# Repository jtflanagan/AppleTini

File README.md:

# AppleTini
An FPGA-based multifunctional card

Earlier iterations of the design used microcontrollers (a Pico and a Teensy 4.1), but we have moved to an FPGA-based design.  The v4 version of the board works in an Apple IIe as a read-only bus dump card.  It reads events on the Apple II bus, and forwards them over USB to a remote host which can process them (including operating as HDMI video-out, similar to the VidHD card).

The v5 board (just ordered!) is intended to provide the full bus feature set.  The ability to read and write data to the bus, as well as perform full DMA and assert all the control lines available (DMA, RES, RDY, INH, IRQ, NMI, and properly implement DMAIN/OUT and INTIN/OUT.

The boards are designed to connect to a stack of Alchitry boards as sold by SparkFun.  The boards have headers which will mate with the Alchitry Br breakout board.  The high-speed USB needed to do bus dumping is provided by the Alchitry Ft board, which is capable of up to 1.6Gbits/sec data transmit over USB3.  The FPGA, and 256MB of DDR3 SDRAM is provided by the Alchitry Au board.

What can this board ultimately do?  Damn near anything.  Shorter term goals are to provide HDMI out, speaker sound, Mockingboard sound, mouse, Ramworks or Slinky style memory expansion, and solid state HDV storage.  Longer term?  CPU Acceleration.  In-circuit Emulator level debugging.  More flexible expanded memory banking techniques.  There's a lot of potential!  The FPGA on the Alchitry Au is an Artix-7 35T, so there's a lot of room for all kinds of stuff.

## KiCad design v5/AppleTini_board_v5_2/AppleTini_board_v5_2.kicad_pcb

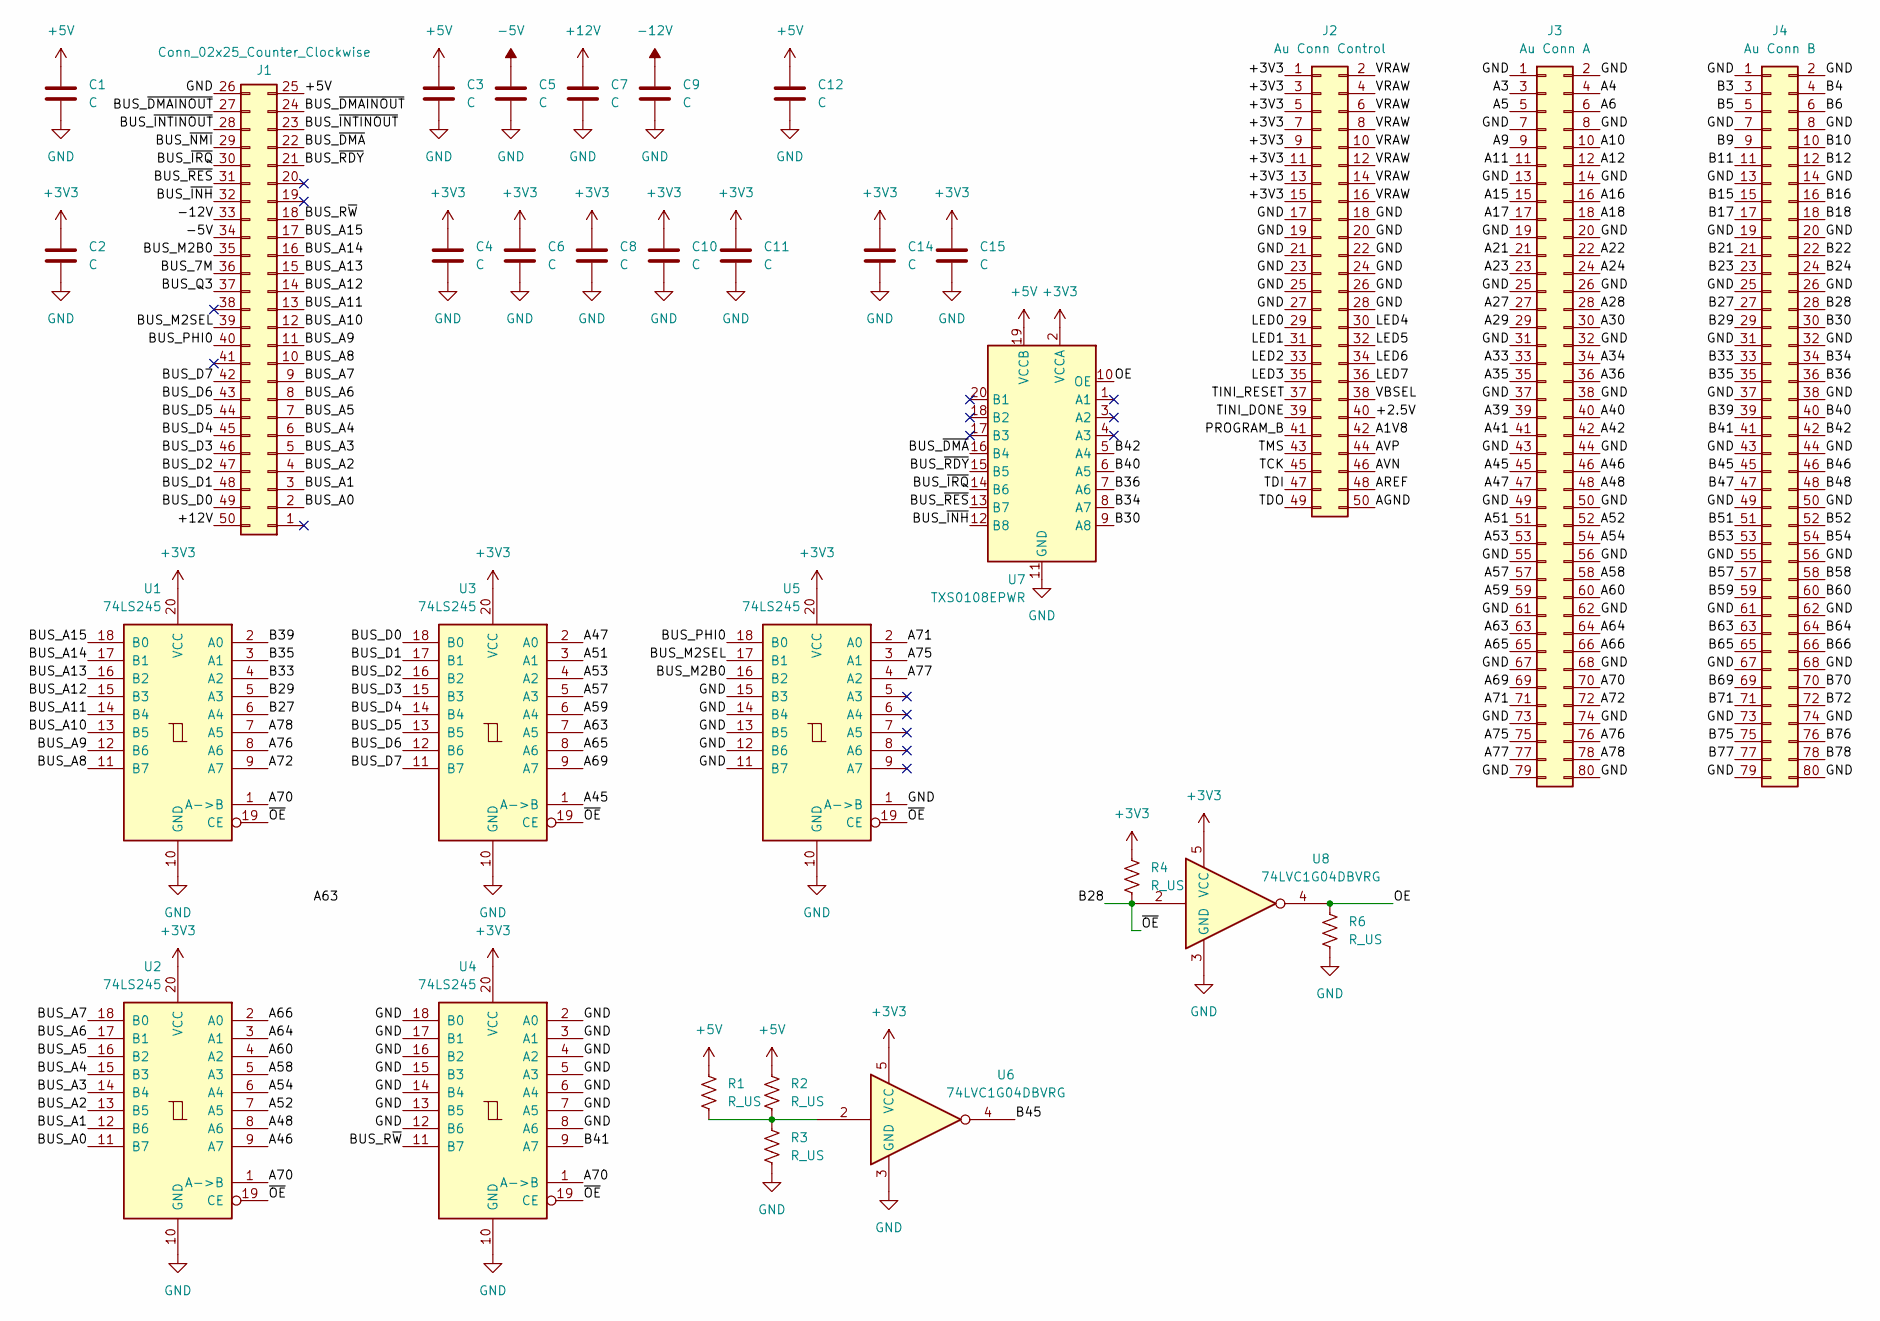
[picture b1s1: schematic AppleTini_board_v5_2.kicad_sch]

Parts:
C1, C2: C; C_0805_2012Metric; LCSC C440198
C3, C4, C5, C6, C7, C8, C9, C10, C11, C12, C14, C15: C; C_0402_1005Metric; LCSC C77020
J1: Conn_02x25_Counter_Clockwise; AppleIIBus_Edge
J2: Au Conn Control; CONN50_6p6X2p9_hdr_HIR; LCSC C424645
J3: Au Conn A; CONN80_17p5X1p85_hdr_HIR; LCSC C294544
J4: Au Conn B; CONN80_17p5X1p85_hdr_HIR; LCSC C294544
R1, R2, R3, R4, R6: R_US; R_0402_1005Metric; LCSC C2991755
U1, U2, U3, U4, U5: 74LS245; TSSOP-20_4.4x6.5mm_P0.65mm; LCSC C6082
U6, U8: 74LVC1G04DBVRG; SOT-353_SC-70-5; LCSC C264081
U7: TXS0108EPWR; TSSOP-20_4.4x6.5mm_P0.65mm; LCSC C17206

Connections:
+3V3: C2.1, C4.1, C6.1, C8.1, C10.1, C11.1, C14.1, C15.1, J2.1, J2.3, J2.5, J2.7, J2.9, J2.11, J2.13, J2.15, R4.1, U1.20 (VCC), U2.20 (VCC), U3.20 (VCC), U4.20 (VCC), U5.20 (VCC), U6.5 (VCC), U7.2 (VCCA), U8.5 (VCC)
+5V: C1.1, C3.1, C12.1, J1.25, R1.1, R2.1, U7.19 (VCCB)
+12V: C7.1, J1.50
-5V: C5.1, J1.34
-12V: C9.1, J1.33
/+2.5V: J2.40
/A1V8: J2.42
/A3: J3.3
/A4: J3.4
/A5: J3.5
/A6: J3.6
/A9: J3.9
/A10: J3.10
/A11: J3.11
/A12: J3.12
/A15: J3.15
/A16: J3.16
/A17: J3.17
/A18: J3.18
/A21: J3.21
/A22: J3.22
/A23: J3.23
/A24: J3.24
/A27: J3.27
/A28: J3.28
/A29: J3.29
/A30: J3.30
/A33: J3.33
/A34: J3.34
/A35: J3.35
/A36: J3.36
/A39: J3.39
/A40: J3.40
/A41: J3.41
/A42: J3.42
/A45: J3.45, U3.1 (A->B)
/A46: J3.46, U2.9 (A7)
/A47: J3.47, U3.2 (A0)
/A48: J3.48, U2.8 (A6)
/A51: J3.51, U3.3 (A1)
/A52: J3.52, U2.7 (A5)
/A53: J3.53, U3.4 (A2)
/A54: J3.54, U2.6 (A4)
/A57: J3.57, U3.5 (A3)
/A58: J3.58, U2.5 (A3)
/A59: J3.59, U3.6 (A4)
/A60: J3.60, U2.4 (A2)
/A63: J3.63, U3.7 (A5)
/A64: J3.64, U2.3 (A1)
/A65: J3.65, U3.8 (A6)
/A66: J3.66, U2.2 (A0)
/A69: J3.69, U3.9 (A7)
/A70: J3.70, U1.1 (A->B), U2.1 (A->B), U4.1 (A->B)
/A71: J3.71, U5.2 (A0)
/A72: J3.72, U1.9 (A7)
/A75: J3.75, U5.3 (A1)
/A76: J3.76, U1.8 (A6)
/A77: J3.77, U5.4 (A2)
/A78: J3.78, U1.7 (A5)
/AGND: J2.50
/AREF: J2.48
/AVN: J2.46
/AVP: J2.44
/B3: J4.3
/B4: J4.4
/B5: J4.5
/B6: J4.6
/B9: J4.9
/B10: J4.10
/B11: J4.11
/B12: J4.12
/B15: J4.15
/B16: J4.16
/B17: J4.17
/B18: J4.18
/B21: J4.21
/B22: J4.22
/B23: J4.23
/B24: J4.24
/B27: J4.27, U1.6 (A4)
/B28: J4.28, R4.2, U1.19 (CE), U2.19 (CE), U3.19 (CE), U4.19 (CE), U5.19 (CE), U8.2
/B29: J4.29, U1.5 (A3)
/B30: J4.30, U7.9 (A8)
/B33: J4.33, U1.4 (A2)
/B34: J4.34, U7.8 (A7)
/B35: J4.35, U1.3 (A1)
/B36: J4.36, U7.7 (A6)
/B39: J4.39, U1.2 (A0)
/B40: J4.40, U7.6 (A5)
/B41: J4.41, U4.9 (A7)
/B42: J4.42, U7.5 (A4)
/B45: J4.45, U6.4
/B46: J4.46
/B47: J4.47
/B48: J4.48
/B51: J4.51
/B52: J4.52
/B53: J4.53
/B54: J4.54
/B57: J4.57
/B58: J4.58
/B59: J4.59
/B60: J4.60
/B63: J4.63
/B64: J4.64
/B65: J4.65
/B66: J4.66
/B69: J4.69
/B70: J4.70
/B71: J4.71
/B72: J4.72
/B75: J4.75
/B76: J4.76
/B77: J4.77
/B78: J4.78
/BUS_7M: J1.36
/BUS_A0: J1.2, U2.11 (B7)
/BUS_A1: J1.3, U2.12 (B6)
/BUS_A2: J1.4, U2.13 (B5)
/BUS_A3: J1.5, U2.14 (B4)
/BUS_A4: J1.6, U2.15 (B3)
/BUS_A5: J1.7, U2.16 (B2)
/BUS_A6: J1.8, U2.17 (B1)
/BUS_A7: J1.9, U2.18 (B0)
/BUS_A8: J1.10, U1.11 (B7)
/BUS_A9: J1.11, U1.12 (B6)
/BUS_A10: J1.12, U1.13 (B5)
/BUS_A11: J1.13, U1.14 (B4)
/BUS_A12: J1.14, U1.15 (B3)
/BUS_A13: J1.15, U1.16 (B2)
/BUS_A14: J1.16, U1.17 (B1)
/BUS_A15: J1.17, U1.18 (B0)
/BUS_D0: J1.49, U3.18 (B0)
/BUS_D1: J1.48, U3.17 (B1)
/BUS_D2: J1.47, U3.16 (B2)
/BUS_D3: J1.46, U3.15 (B3)
/BUS_D4: J1.45, U3.14 (B4)
/BUS_D5: J1.44, U3.13 (B5)
/BUS_D6: J1.43, U3.12 (B6)
/BUS_D7: J1.42, U3.11 (B7)
/BUS_M2B0: J1.35, U5.16 (B2)
/BUS_M2SEL: J1.39, U5.17 (B1)
/BUS_PHI0: J1.40, U5.18 (B0)
/BUS_Q3: J1.37
/BUS_R~W: J1.18, U4.11 (B7)
/BUS_~DMAINOUT: J1.24, J1.27
/BUS_~DMA: J1.22, U7.16 (B4)
/BUS_~INH: J1.32, U7.12 (B8)
/BUS_~INTINOUT: J1.23, J1.28
/BUS_~IRQ: J1.30, U7.14 (B6)
/BUS_~NMI: J1.29
/BUS_~RDY: J1.21, U7.15 (B5)
/BUS_~RES: J1.31, U7.13 (B7)
/LED0: J2.29
/LED1: J2.31
/LED2: J2.33
/LED3: J2.35
/LED4: J2.30
/LED5: J2.32
/LED6: J2.34
/LED7: J2.36
/OE: R6.1, U7.10 (OE), U8.4
/PROGRAM_B: J2.41
/TCK: J2.45
/TDI: J2.47
/TDO: J2.49
/TINI_DONE: J2.39
/TINI_RESET: J2.37
/TMS: J2.43
/VBSEL: J2.38
/VRAW: J2.2, J2.4, J2.6, J2.8, J2.10, J2.12, J2.14, J2.16
GND: C1.2, C2.2, C3.2, C4.2, C5.2, C6.2, C7.2, C8.2, C9.2, C10.2, C11.2, C12.2, C14.2, C15.2, J1.26, J2.17, J2.18, J2.19, J2.20, J2.21, J2.22, J2.23, J2.24, J2.25, J2.26, J2.27, J2.28, J3.1, J3.2, J3.7, J3.8, J3.13, J3.14, J3.19, J3.20, J3.25, J3.26, J3.31, J3.32, J3.37, J3.38, J3.43, J3.44, J3.49, J3.50, J3.55, J3.56, J3.61, J3.62, J3.67, J3.68, J3.73, J3.74, J3.79, J3.80, J4.1, J4.2, J4.7, J4.8, J4.13, J4.14, J4.19, J4.20, J4.25, J4.26, J4.31, J4.32, J4.37, J4.38, J4.43, J4.44, J4.49, J4.50, J4.55, J4.56, J4.61, J4.62, J4.67, J4.68, J4.73, J4.74, J4.79, J4.80, R3.2, R6.2, U1.10 (GND), U2.10 (GND), U3.10 (GND), U4.2 (A0), U4.3 (A1), U4.4 (A2), U4.5 (A3), U4.6 (A4), U4.7 (A5), U4.8 (A6), U4.10 (GND), U4.12 (B6), U4.13 (B5), U4.14 (B4), U4.15 (B3), U4.16 (B2), U4.17 (B1), U4.18 (B0), U5.1 (A->B), U5.10 (GND), U5.11 (B7), U5.12 (B6), U5.13 (B5), U5.14 (B4), U5.15 (B3), U6.3 (GND), U7.11 (GND), U8.3 (GND)
unnamed: R1.2, R2.2, R3.1, U6.2

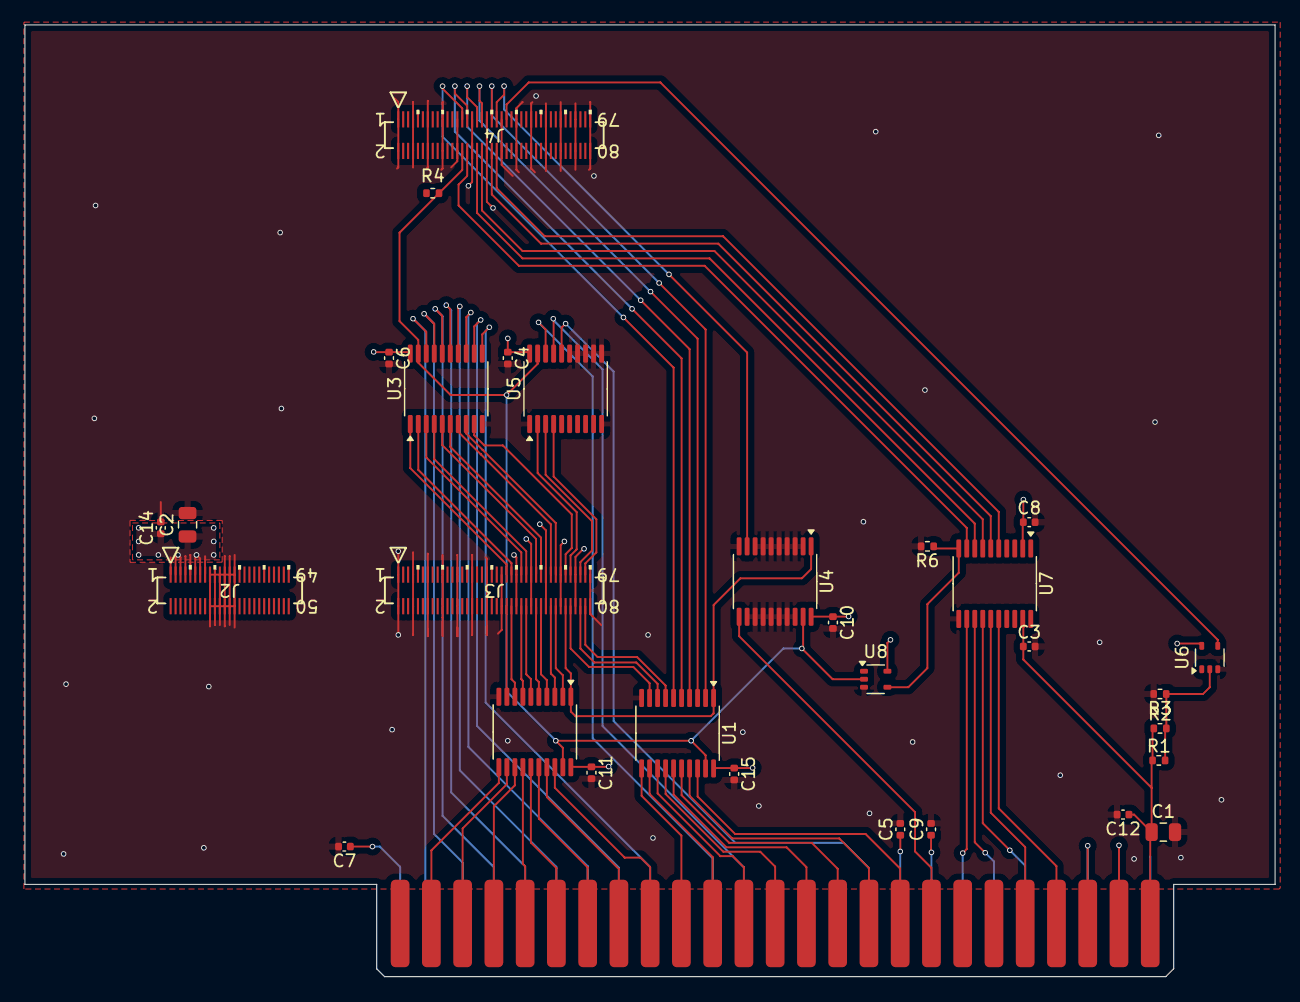
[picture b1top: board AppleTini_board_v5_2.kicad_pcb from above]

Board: 4 copper layers, 101.6 x 77.3 mm, 31 parts (0 on the bottom side), 81 nets.

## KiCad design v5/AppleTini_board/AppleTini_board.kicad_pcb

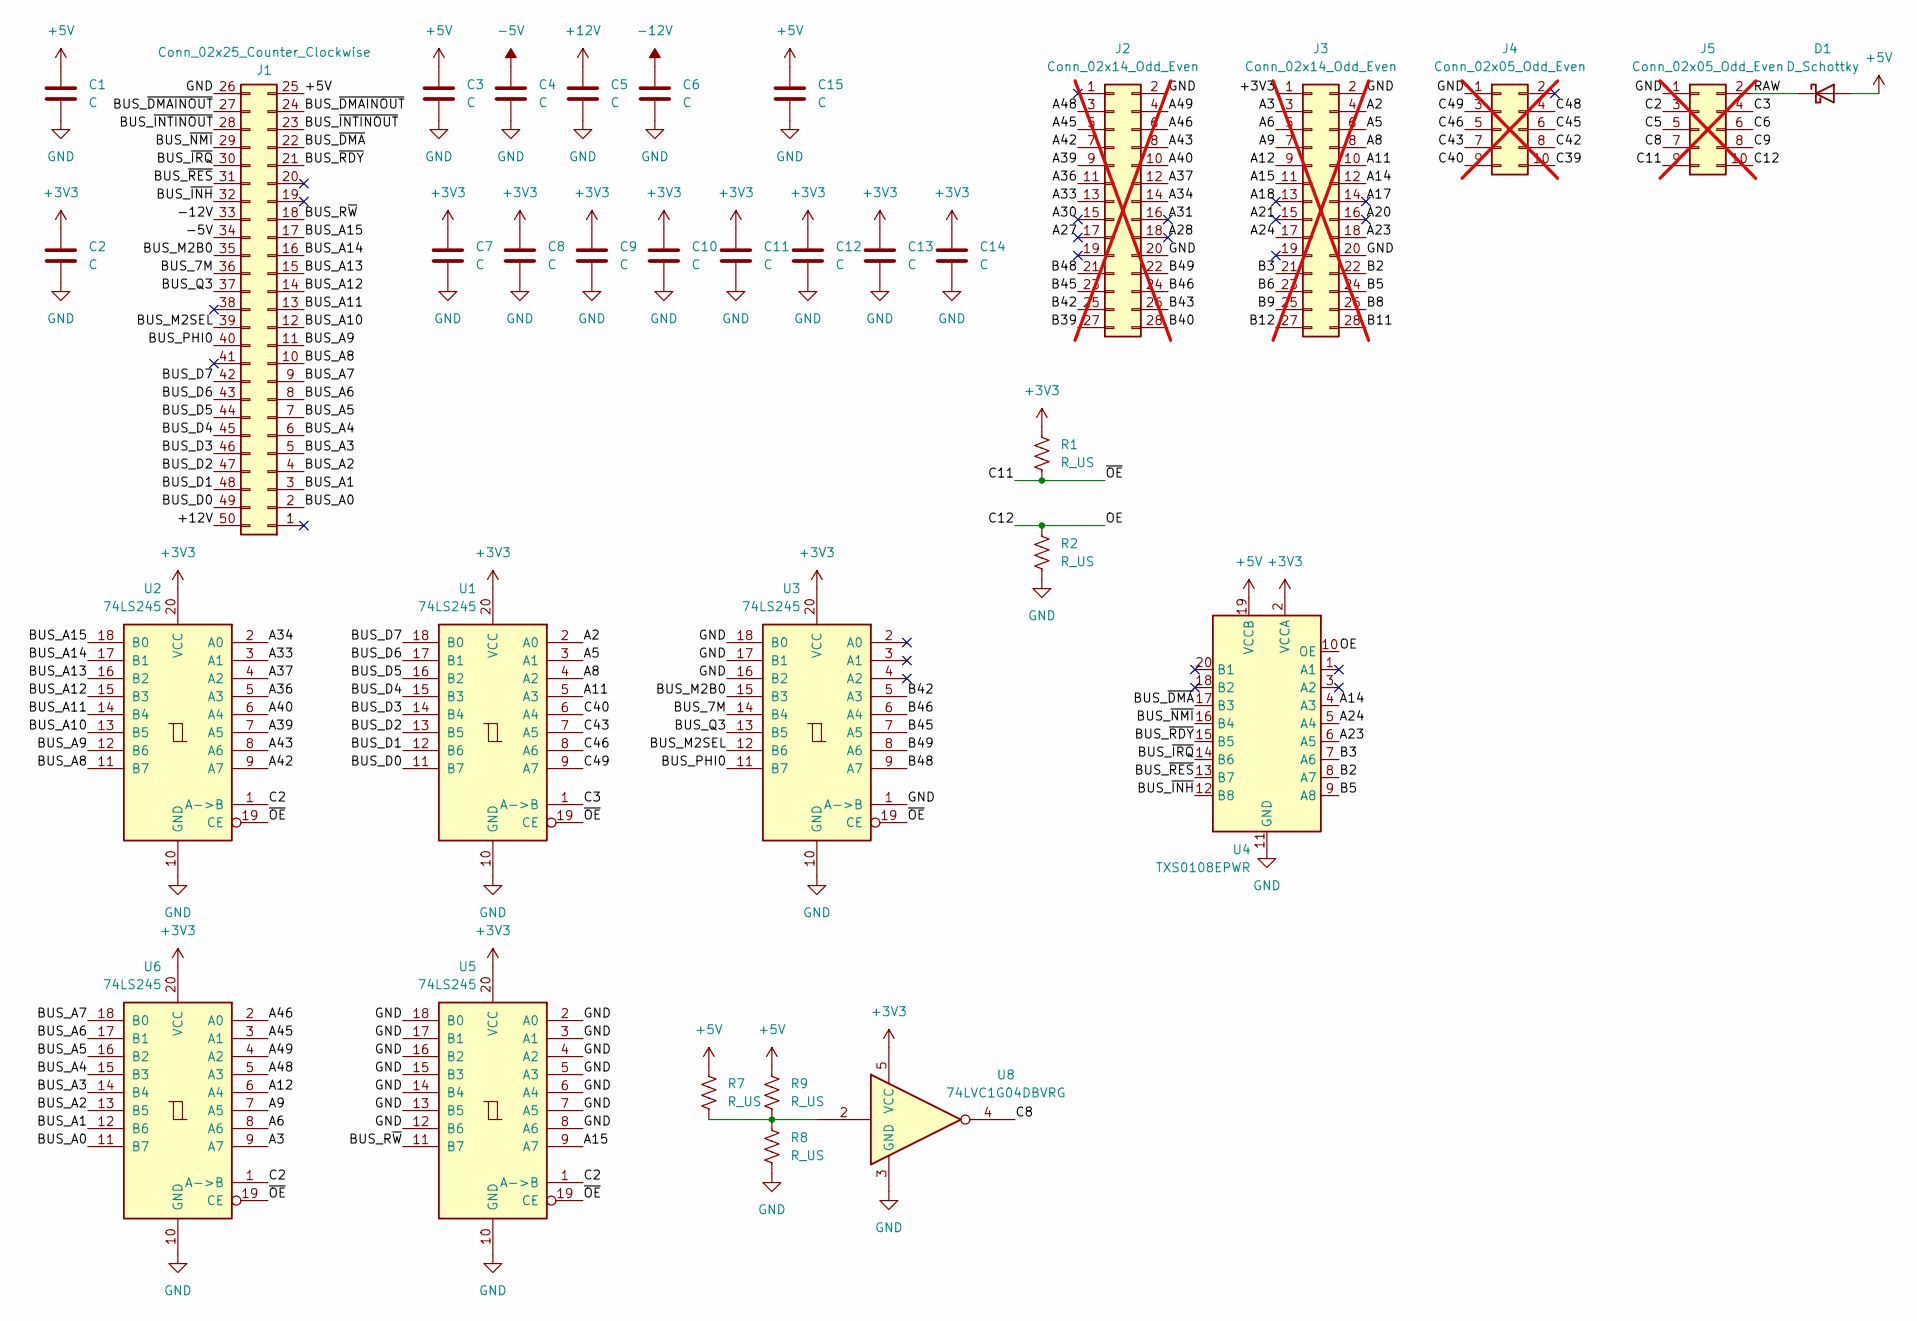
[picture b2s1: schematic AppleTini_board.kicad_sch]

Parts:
C1, C2: C; C_0805_2012Metric; LCSC C440198
C3, C4, C5, C6, C7, C8, C9, C10, C11, C12, C13, C14, C15: C; C_0402_1005Metric; LCSC C77020
D1: D_Schottky; Nexperia_CFP3_SOD-123W; LCSC C82288
J1: Conn_02x25_Counter_Clockwise; AppleIIBus_Edge
J2, J3: Conn_02x14_Odd_Even; PinHeader_2x14_P2.54mm_Vertical; not fitted
J4, J5: Conn_02x05_Odd_Even; PinHeader_2x05_P2.54mm_Vertical; not fitted
R1, R2, R7, R8, R9: R_US; R_0402_1005Metric; LCSC C2991755
U1, U2, U3, U5, U6: 74LS245; TSSOP-20_4.4x6.5mm_P0.65mm; LCSC C6082
U4: TXS0108EPWR; TSSOP-20_4.4x6.5mm_P0.65mm; LCSC C17206
U8: 74LVC1G04DBVRG; SOT-23-5

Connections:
+3V3: C2.1, C7.1, C8.1, C9.1, C10.1, C11.1, C12.1, C13.1, C14.1, J3.1, R1.1, U1.20 (VCC), U2.20 (VCC), U3.20 (VCC), U4.2 (VCCA), U5.20 (VCC), U6.20 (VCC), U8.5 (VCC)
+5V: C1.1, C3.1, C15.1, D1.2 (A), J1.25, R7.1, R9.1, U4.19 (VCCB)
+12V: C5.1, J1.50
-5V: C4.1, J1.34
-12V: C6.1, J1.33
/A2: J3.4, U1.2 (A0)
/A3: J3.3, U6.9 (A7)
/A5: J3.6, U1.3 (A1)
/A6: J3.5, U6.8 (A6)
/A8: J3.8, U1.4 (A2)
/A9: J3.7, U6.7 (A5)
/A11: J3.10, U1.5 (A3)
/A12: J3.9, U6.6 (A4)
/A14: J3.12, U4.4 (A3)
/A15: J3.11, U5.9 (A7)
/A17: J3.14
/A18: J3.13
/A20: J3.16
/A21: J3.15
/A23: J3.18, U4.6 (A5)
/A24: J3.17, U4.5 (A4)
/A27: J2.17
/A28: J2.18
/A30: J2.15
/A31: J2.16
/A33: J2.13, U2.3 (A1)
/A34: J2.14, U2.2 (A0)
/A36: J2.11, U2.5 (A3)
/A37: J2.12, U2.4 (A2)
/A39: J2.9, U2.7 (A5)
/A40: J2.10, U2.6 (A4)
/A42: J2.7, U2.9 (A7)
/A43: J2.8, U2.8 (A6)
/A45: J2.5, U6.3 (A1)
/A46: J2.6, U6.2 (A0)
/A48: J2.3, U6.5 (A3)
/A49: J2.4, U6.4 (A2)
/B2: J3.22, U4.8 (A7)
/B3: J3.21, U4.7 (A6)
/B5: J3.24, U4.9 (A8)
/B6: J3.23
/B8: J3.26
/B9: J3.25
/B11: J3.28
/B12: J3.27
/B39: J2.27
/B40: J2.28
/B42: J2.25, U3.5 (A3)
/B43: J2.26
/B45: J2.23, U3.7 (A5)
/B46: J2.24, U3.6 (A4)
/B48: J2.21, U3.9 (A7)
/B49: J2.22, U3.8 (A6)
/BUS_7M: J1.36, U3.14 (B4)
/BUS_A0: J1.2, U6.11 (B7)
/BUS_A1: J1.3, U6.12 (B6)
/BUS_A2: J1.4, U6.13 (B5)
/BUS_A3: J1.5, U6.14 (B4)
/BUS_A4: J1.6, U6.15 (B3)
/BUS_A5: J1.7, U6.16 (B2)
/BUS_A6: J1.8, U6.17 (B1)
/BUS_A7: J1.9, U6.18 (B0)
/BUS_A8: J1.10, U2.11 (B7)
/BUS_A9: J1.11, U2.12 (B6)
/BUS_A10: J1.12, U2.13 (B5)
/BUS_A11: J1.13, U2.14 (B4)
/BUS_A12: J1.14, U2.15 (B3)
/BUS_A13: J1.15, U2.16 (B2)
/BUS_A14: J1.16, U2.17 (B1)
/BUS_A15: J1.17, U2.18 (B0)
/BUS_D0: J1.49, U1.11 (B7)
/BUS_D1: J1.48, U1.12 (B6)
/BUS_D2: J1.47, U1.13 (B5)
/BUS_D3: J1.46, U1.14 (B4)
/BUS_D4: J1.45, U1.15 (B3)
/BUS_D5: J1.44, U1.16 (B2)
/BUS_D6: J1.43, U1.17 (B1)
/BUS_D7: J1.42, U1.18 (B0)
/BUS_M2B0: J1.35, U3.15 (B3)
/BUS_M2SEL: J1.39, U3.12 (B6)
/BUS_PHI0: J1.40, U3.11 (B7)
/BUS_Q3: J1.37, U3.13 (B5)
/BUS_R~W: J1.18, U5.11 (B7)
/BUS_~DMAINOUT: J1.24, J1.27
/BUS_~DMA: J1.22, U4.17 (B3)
/BUS_~INH: J1.32, U4.12 (B8)
/BUS_~INTINOUT: J1.23, J1.28
/BUS_~IRQ: J1.30, U4.14 (B6)
/BUS_~NMI: J1.29, U4.16 (B4)
/BUS_~RDY: J1.21, U4.15 (B5)
/BUS_~RES: J1.31, U4.13 (B7)
/C2: J5.3, U2.1 (A->B), U5.1 (A->B), U6.1 (A->B)
/C3: J5.4, U1.1 (A->B)
/C5: J5.5
/C6: J5.6
/C8: J5.7, U8.4
/C9: J5.8
/C11: J5.9, R1.2, U1.19 (CE), U2.19 (CE), U3.19 (CE), U5.19 (CE), U6.19 (CE)
/C12: J5.10, R2.1, U4.10 (OE)
/C39: J4.10
/C40: J4.9, U1.6 (A4)
/C42: J4.8
/C43: J4.7, U1.7 (A5)
/C45: J4.6
/C46: J4.5, U1.8 (A6)
/C48: J4.4
/C49: J4.3, U1.9 (A7)
/RAW: D1.1 (K), J5.2
GND: C1.2, C2.2, C3.2, C4.2, C5.2, C6.2, C7.2, C8.2, C9.2, C10.2, C11.2, C12.2, C13.2, C14.2, C15.2, J1.26, J2.2, J2.20, J3.2, J3.20, J4.1, J5.1, R2.2, R8.2, U1.10 (GND), U2.10 (GND), U3.1 (A->B), U3.10 (GND), U3.16 (B2), U3.17 (B1), U3.18 (B0), U4.11 (GND), U5.2 (A0), U5.3 (A1), U5.4 (A2), U5.5 (A3), U5.6 (A4), U5.7 (A5), U5.8 (A6), U5.10 (GND), U5.12 (B6), U5.13 (B5), U5.14 (B4), U5.15 (B3), U5.16 (B2), U5.17 (B1), U5.18 (B0), U6.10 (GND), U8.3 (GND)
unnamed: R7.2, R8.1, R9.2, U8.2

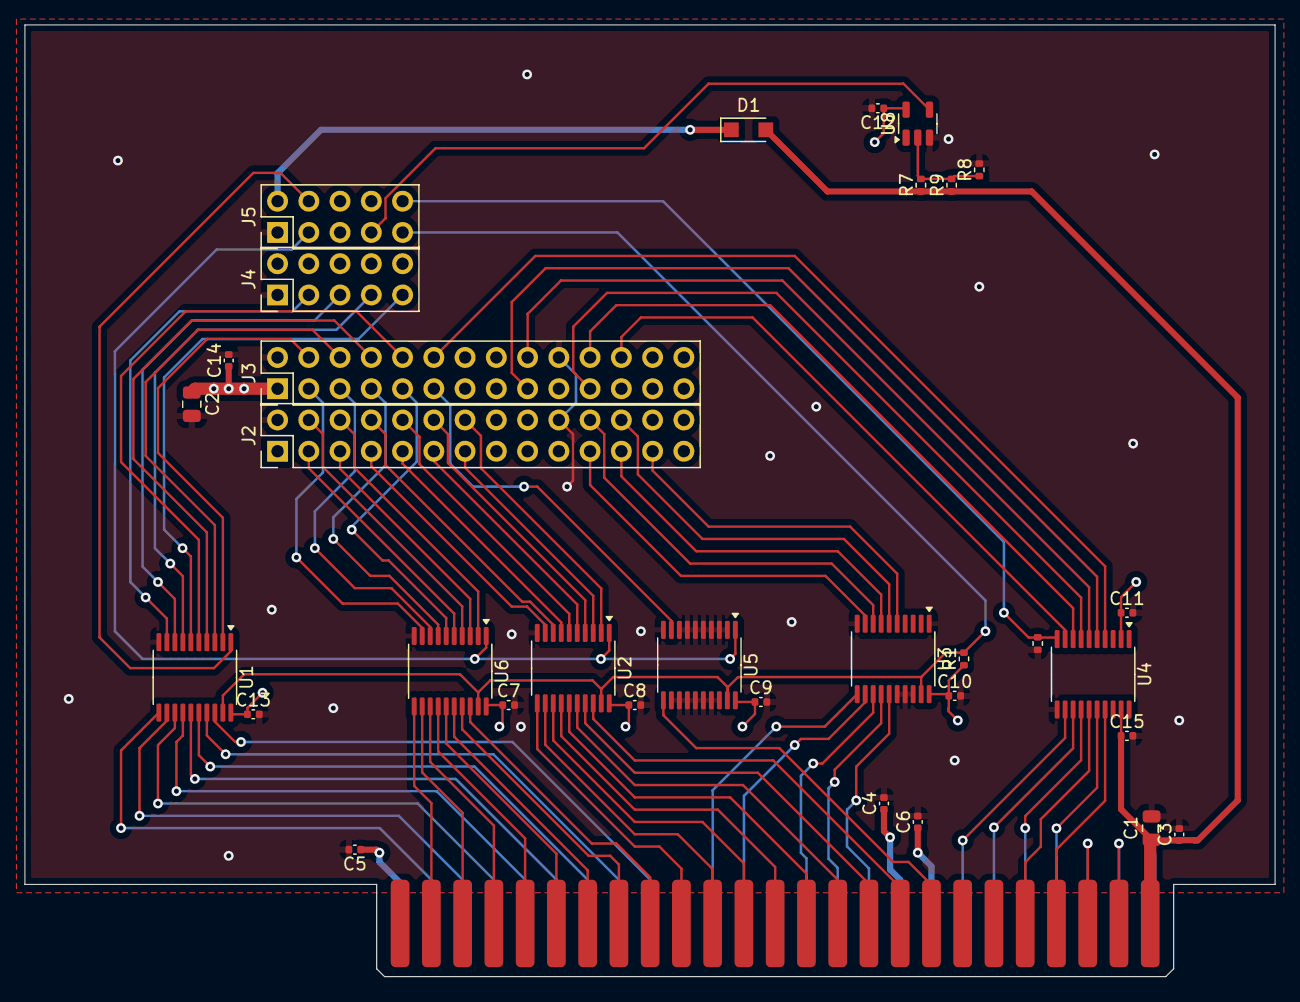
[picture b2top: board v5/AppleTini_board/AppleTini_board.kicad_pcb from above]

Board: 4 copper layers, 101.6 x 77.3 mm, 33 parts (0 on the bottom side), 87 nets.

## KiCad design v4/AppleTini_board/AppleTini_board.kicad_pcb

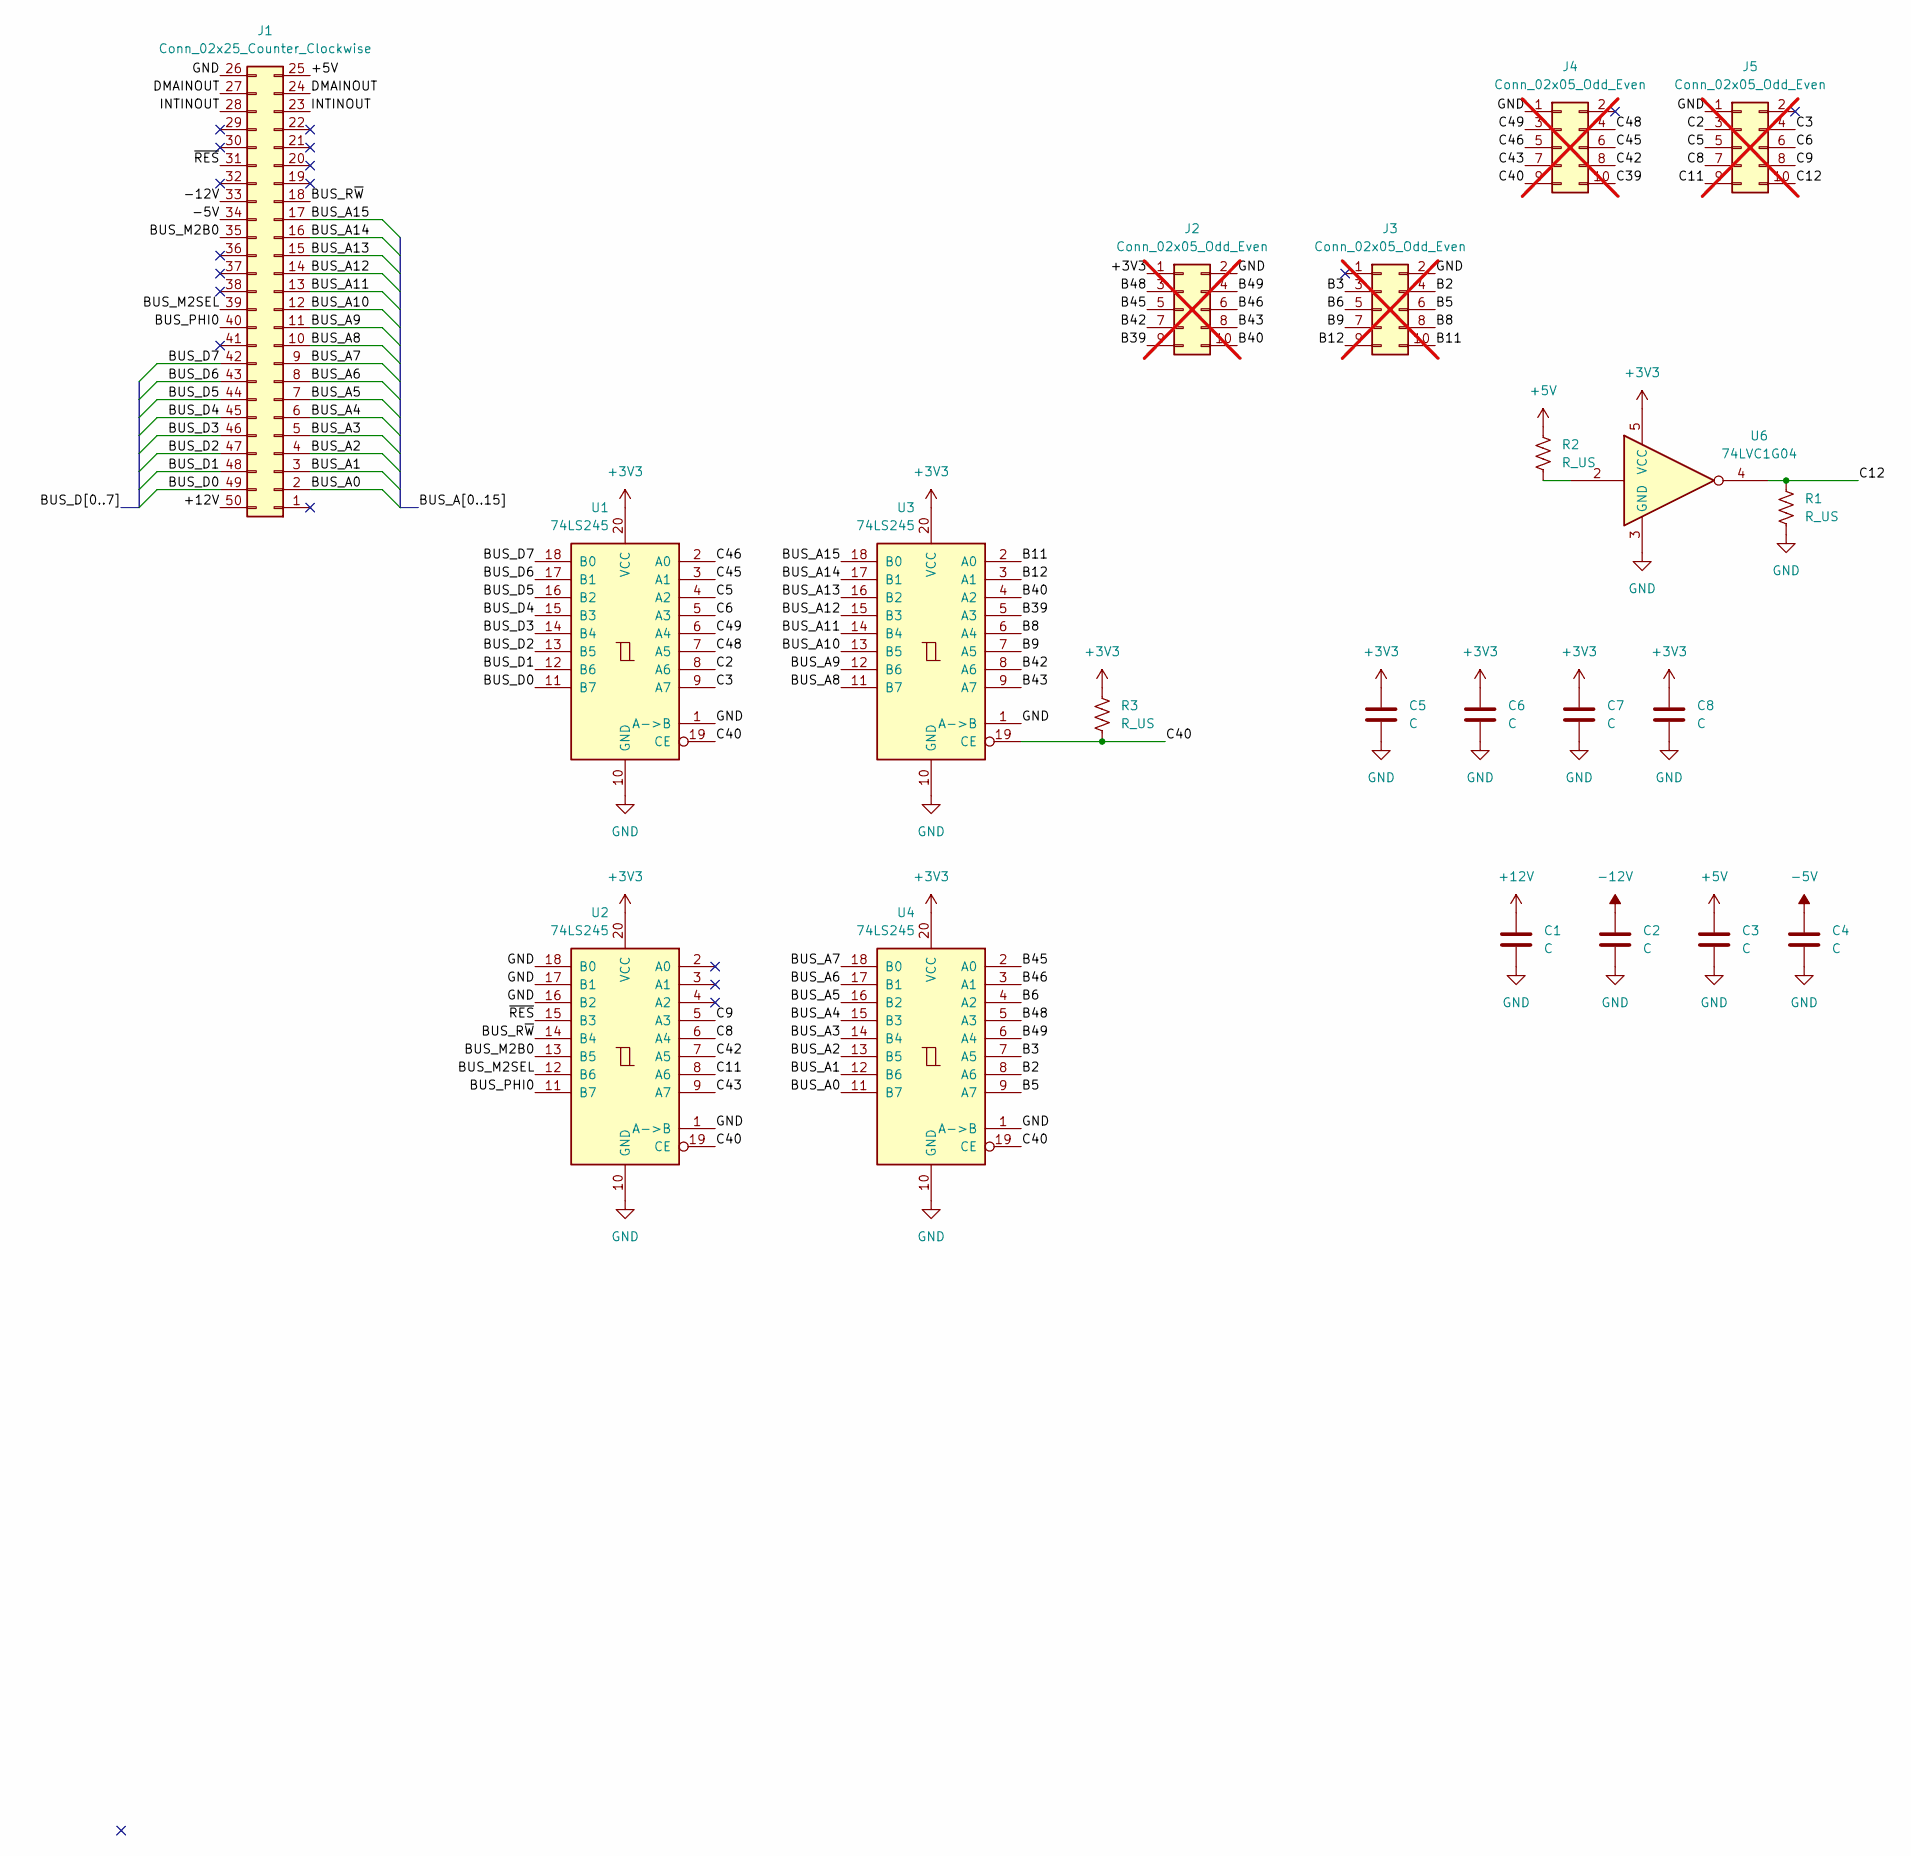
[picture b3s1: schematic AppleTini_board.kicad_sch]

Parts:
C1, C2, C3, C4, C5, C6, C7, C8: C; C_1206_3216Metric; LCSC C24497
J1: Conn_02x25_Counter_Clockwise; AppleIIBus_Edge
J2, J3, J4, J5: Conn_02x05_Odd_Even; PinHeader_2x05_P2.54mm_Vertical; not fitted
R1, R2, R3: R_US; C_0402_1005Metric; LCSC C2991755
U1, U2, U3, U4: 74LS245; TSSOP-20_4.4x6.5mm_P0.65mm; LCSC C6082
U6: 74LVC1G04; SOT-23-5; LCSC C7826

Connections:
+3V3: C5.1, C6.1, C7.1, C8.1, J2.1, R3.1, U1.20 (VCC), U2.20 (VCC), U3.20 (VCC), U4.20 (VCC), U6.5 (VCC)
+5V: C3.1, J1.25, R2.1
+12V: C1.1, J1.50
-5V: C4.1, J1.34
-12V: C2.1, J1.33
/B2: J3.4, U4.8 (A6)
/B3: J3.3, U4.7 (A5)
/B5: J3.6, U4.9 (A7)
/B6: J3.5, U4.4 (A2)
/B8: J3.8, U3.6 (A4)
/B9: J3.7, U3.7 (A5)
/B11: J3.10, U3.2 (A0)
/B12: J3.9, U3.3 (A1)
/B39: J2.9, U3.5 (A3)
/B40: J2.10, U3.4 (A2)
/B42: J2.7, U3.8 (A6)
/B43: J2.8, U3.9 (A7)
/B45: J2.5, U4.2 (A0)
/B46: J2.6, U4.3 (A1)
/B48: J2.3, U4.5 (A3)
/B49: J2.4, U4.6 (A4)
/BUS_A0: J1.2, U4.11 (B7)
/BUS_A1: J1.3, U4.12 (B6)
/BUS_A2: J1.4, U4.13 (B5)
/BUS_A3: J1.5, U4.14 (B4)
/BUS_A4: J1.6, U4.15 (B3)
/BUS_A5: J1.7, U4.16 (B2)
/BUS_A6: J1.8, U4.17 (B1)
/BUS_A7: J1.9, U4.18 (B0)
/BUS_A8: J1.10, U3.11 (B7)
/BUS_A9: J1.11, U3.12 (B6)
/BUS_A10: J1.12, U3.13 (B5)
/BUS_A11: J1.13, U3.14 (B4)
/BUS_A12: J1.14, U3.15 (B3)
/BUS_A13: J1.15, U3.16 (B2)
/BUS_A14: J1.16, U3.17 (B1)
/BUS_A15: J1.17, U3.18 (B0)
/BUS_D0: J1.49, U1.11 (B7)
/BUS_D1: J1.48, U1.12 (B6)
/BUS_D2: J1.47, U1.13 (B5)
/BUS_D3: J1.46, U1.14 (B4)
/BUS_D4: J1.45, U1.15 (B3)
/BUS_D5: J1.44, U1.16 (B2)
/BUS_D6: J1.43, U1.17 (B1)
/BUS_D7: J1.42, U1.18 (B0)
/BUS_M2B0: J1.35, U2.13 (B5)
/BUS_M2SEL: J1.39, U2.12 (B6)
/BUS_PHI0: J1.40, U2.11 (B7)
/BUS_R~W: J1.18, U2.14 (B4)
/C2: J5.3, U1.8 (A6)
/C3: J5.4, U1.9 (A7)
/C5: J5.5, U1.4 (A2)
/C6: J5.6, U1.5 (A3)
/C8: J5.7, U2.6 (A4)
/C9: J5.8, U2.5 (A3)
/C11: J5.9, U2.8 (A6)
/C12: J5.10, R1.1, U6.4
/C39: J4.10
/C40: J4.9, R3.2, U1.19 (CE), U2.19 (CE), U3.19 (CE), U4.19 (CE)
/C42: J4.8, U2.7 (A5)
/C43: J4.7, U2.9 (A7)
/C45: J4.6, U1.3 (A1)
/C46: J4.5, U1.2 (A0)
/C48: J4.4, U1.7 (A5)
/C49: J4.3, U1.6 (A4)
/DMAINOUT: J1.24, J1.27
/INTINOUT: J1.23, J1.28
/~RES: J1.31, U2.15 (B3)
GND: C1.2, C2.2, C3.2, C4.2, C5.2, C6.2, C7.2, C8.2, J1.26, J2.2, J3.2, J4.1, J5.1, R1.2, U1.1 (A->B), U1.10 (GND), U2.1 (A->B), U2.10 (GND), U2.16 (B2), U2.17 (B1), U2.18 (B0), U3.1 (A->B), U3.10 (GND), U4.1 (A->B), U4.10 (GND), U6.3 (GND)
unnamed: R2.2, U6.2

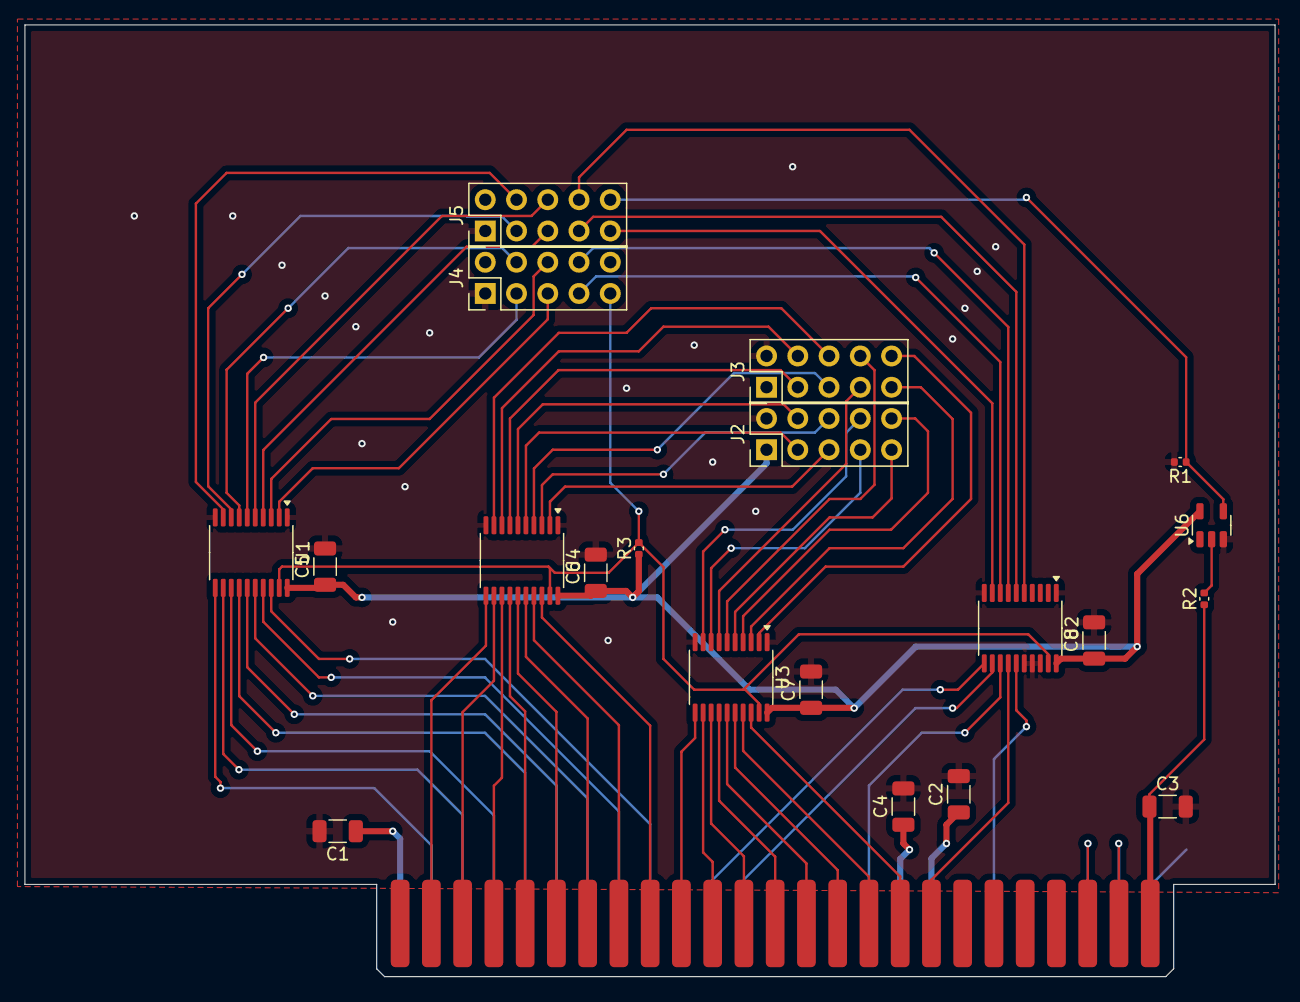
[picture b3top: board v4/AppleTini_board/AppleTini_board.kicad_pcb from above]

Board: 2 copper layers, 101.6 x 77.3 mm, 21 parts (0 on the bottom side), 69 nets.
